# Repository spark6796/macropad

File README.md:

This is an awesome macropad with 8 buttons, 1 rotary encoder, and an OLED screen. All keys have RGB LEDs, with extra indicator LEDs at the top to show status. It runs on KMK firmware and is fully customizable.

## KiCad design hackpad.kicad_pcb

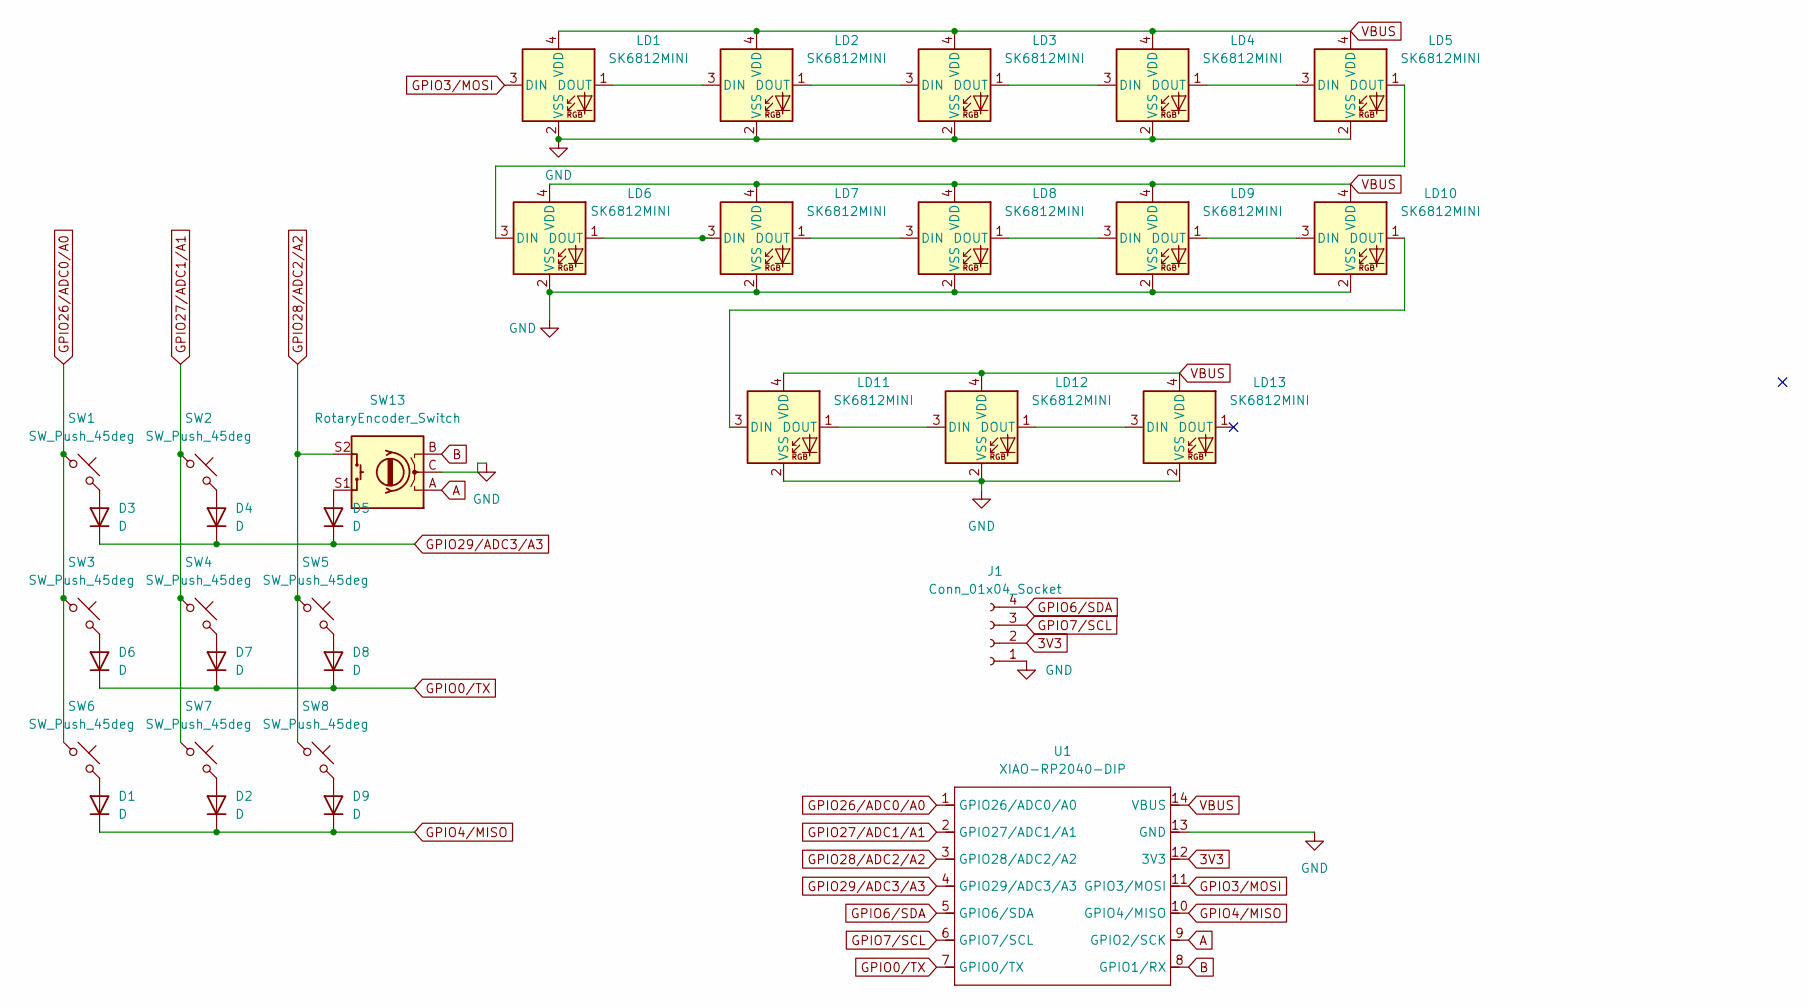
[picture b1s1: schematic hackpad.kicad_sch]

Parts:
D1, D2, D3, D4, D5, D6, D7, D8, D9: D; D_A-405_P10.16mm_Horizontal
J1: Conn_01x04_Socket; SSD1306-0.91-OLED-4pin-128x32
LD1, LD2, LD3, LD4, LD5, LD6, LD7, LD8, LD9, LD10, LD11, LD12, LD13: SK6812MINI; SK6812-MINI-E
SW1, SW2, SW3, SW4, SW5, SW6, SW7, SW8: SW_Push_45deg; SW_Cherry_MX_1.00u_PCB
SW13: RotaryEncoder_Switch; RotaryEncoder_Alps_EC11E-Switch_Vertical_H20mm
U1: XIAO-RP2040-DIP

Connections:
3V3: J1.2, U1.12 (3V3)
A: SW13.A, U1.9 (GPIO2/SCK)
B: SW13.B, U1.8 (GPIO1/RX)
GND: J1.1, LD1.2 (VSS), LD2.2 (VSS), LD3.2 (VSS), LD4.2 (VSS), LD5.2 (VSS), LD6.2 (VSS), LD7.2 (VSS), LD8.2 (VSS), LD9.2 (VSS), LD10.2 (VSS), LD11.2 (VSS), LD12.2 (VSS), LD13.2 (VSS), SW13.C, U1.13 (GND)
GPIO0/TX: D6.1 (K), D7.1 (K), D8.1 (K), U1.7 (GPIO0/TX)
GPIO3/MOSI: LD1.3 (DIN), U1.11 (GPIO3/MOSI)
GPIO4/MISO: D1.1 (K), D2.1 (K), D9.1 (K), U1.10 (GPIO4/MISO)
GPIO6/SDA: J1.4, U1.5 (GPIO6/SDA)
GPIO7/SCL: J1.3, U1.6 (GPIO7/SCL)
GPIO26/ADC0/A0: SW1.1, SW3.1, SW6.1, U1.1 (GPIO26/ADC0/A0)
GPIO27/ADC1/A1: SW2.1, SW4.1, SW7.1, U1.2 (GPIO27/ADC1/A1)
GPIO28/ADC2/A2: SW5.1, SW8.1, SW13.S2, U1.3 (GPIO28/ADC2/A2)
GPIO29/ADC3/A3: D3.1 (K), D4.1 (K), D5.1 (K), U1.4 (GPIO29/ADC3/A3)
unnamed: D1.2 (A), SW6.2
unnamed: D2.2 (A), SW7.2
unnamed: D3.2 (A), SW1.2
unnamed: D4.2 (A), SW2.2
unnamed: D5.2 (A), SW13.S1
unnamed: D6.2 (A), SW3.2
unnamed: D7.2 (A), SW4.2
unnamed: D8.2 (A), SW5.2
unnamed: D9.2 (A), SW8.2
unnamed: LD1.1 (DOUT), LD2.3 (DIN)
unnamed: LD2.1 (DOUT), LD3.3 (DIN)
unnamed: LD3.1 (DOUT), LD4.3 (DIN)
unnamed: LD4.1 (DOUT), LD5.3 (DIN)
unnamed: LD5.1 (DOUT), LD6.3 (DIN)
unnamed: LD6.1 (DOUT), LD7.3 (DIN)
unnamed: LD7.1 (DOUT), LD8.3 (DIN)
unnamed: LD8.1 (DOUT), LD9.3 (DIN)
unnamed: LD9.1 (DOUT), LD10.3 (DIN)
unnamed: LD10.1 (DOUT), LD11.3 (DIN)
unnamed: LD11.1 (DOUT), LD12.3 (DIN)
unnamed: LD12.1 (DOUT), LD13.3 (DIN)
VBUS: LD1.4 (VDD), LD2.4 (VDD), LD3.4 (VDD), LD4.4 (VDD), LD5.4 (VDD), LD6.4 (VDD), LD7.4 (VDD), LD8.4 (VDD), LD9.4 (VDD), LD10.4 (VDD), LD11.4 (VDD), LD12.4 (VDD), LD13.4 (VDD), U1.14 (VBUS)

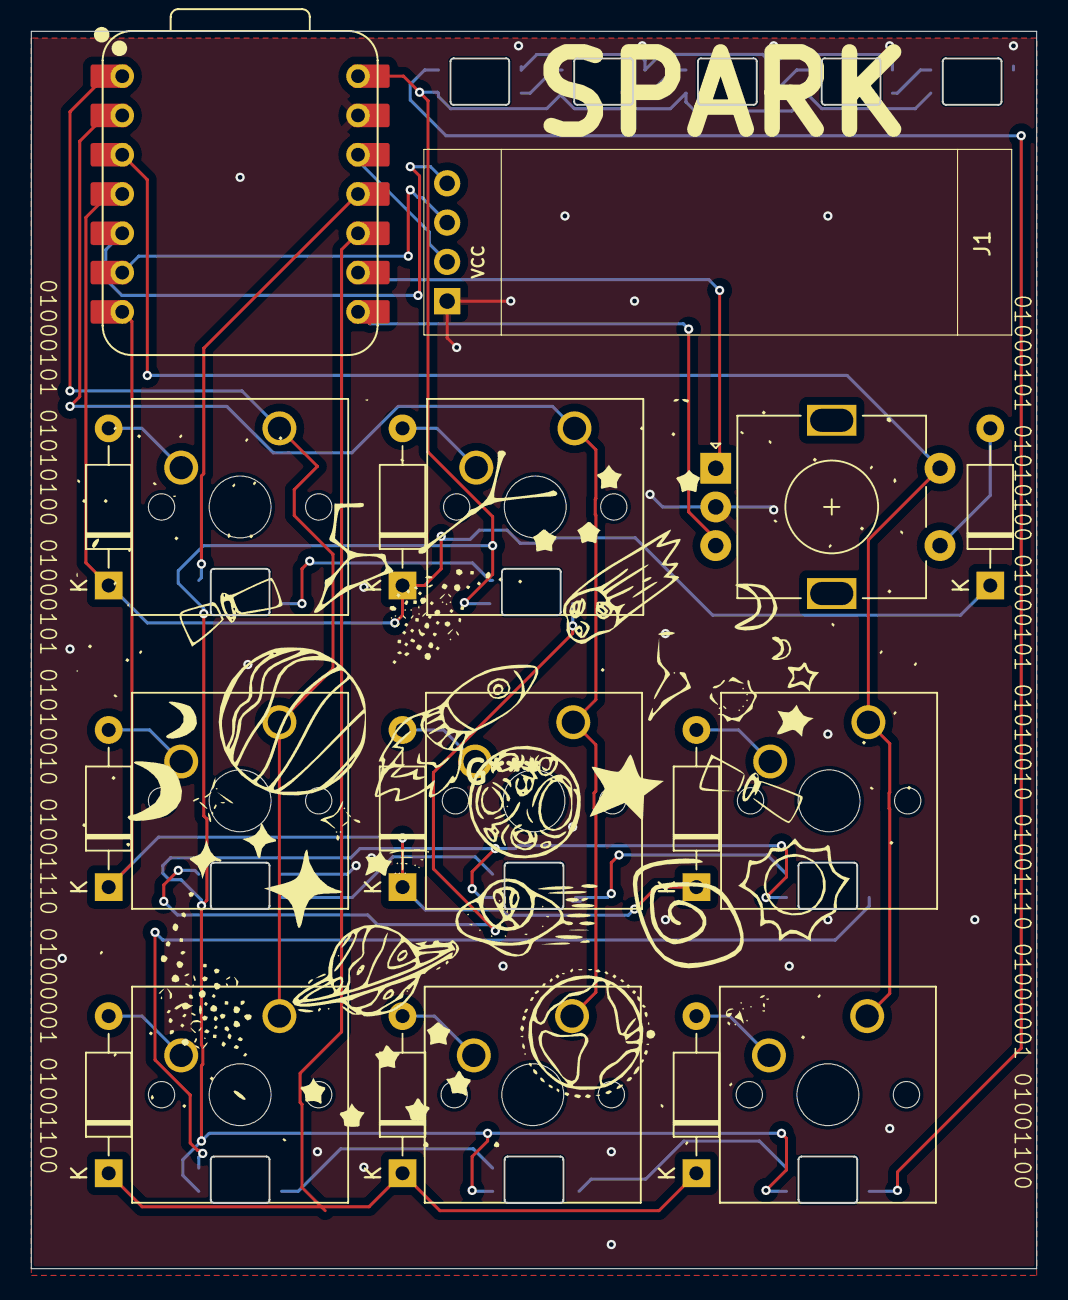
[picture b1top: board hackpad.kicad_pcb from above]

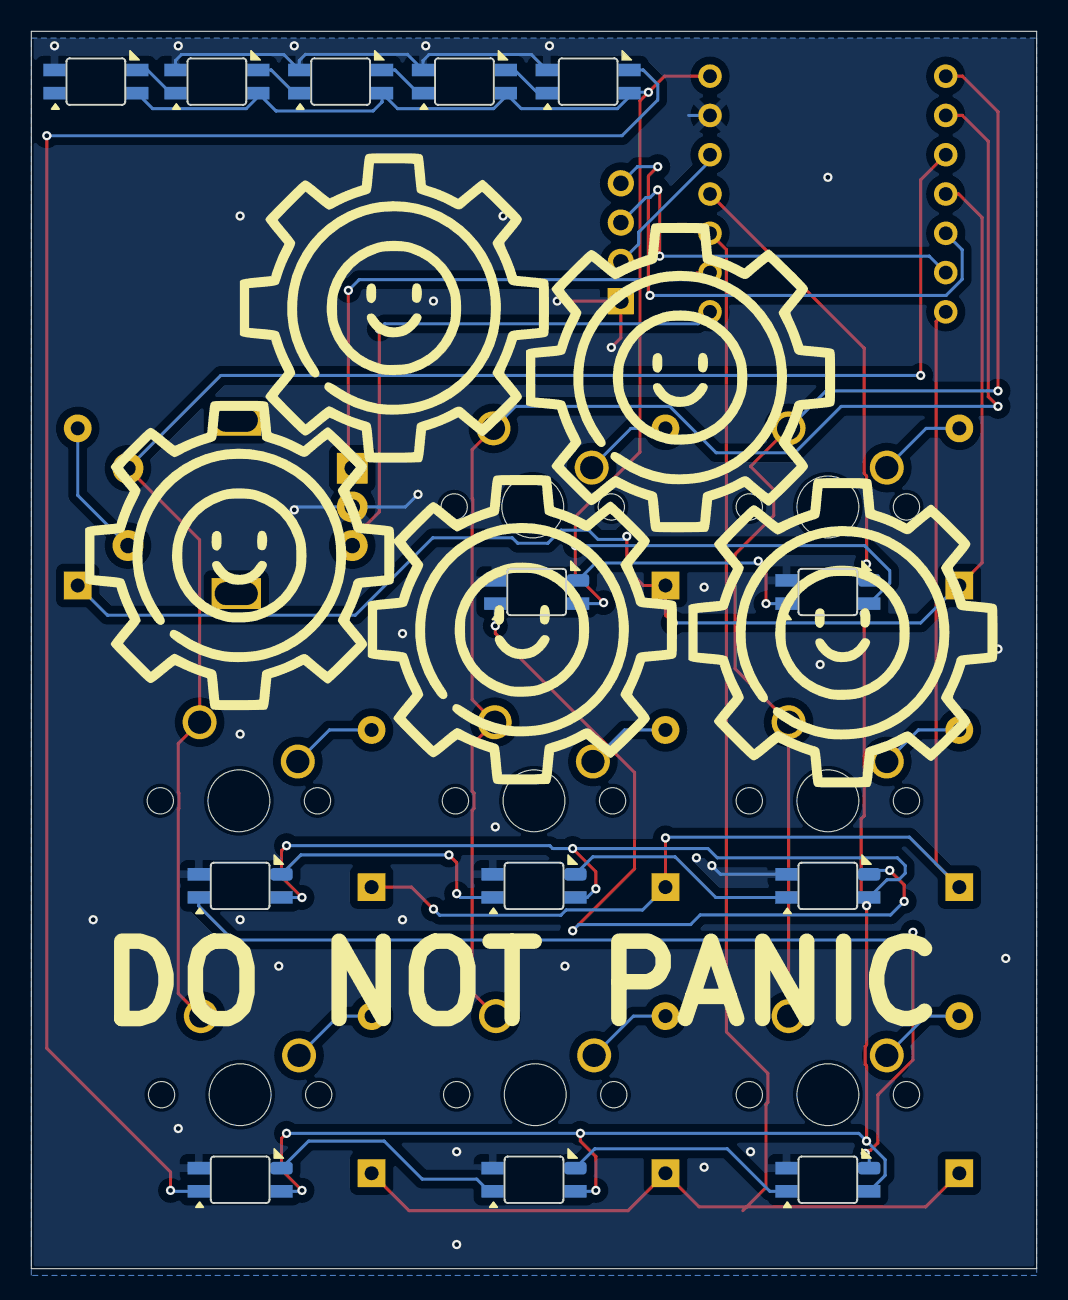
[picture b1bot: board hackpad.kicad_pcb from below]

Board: 2 copper layers, 65.0 x 80.0 mm, 33 parts (13 on the bottom side), 35 nets.

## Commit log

2025-12-18 chore: Remove duplicate files
2025-12-18 Add PCB images
2025-12-18 Add PCB top view image to README
2025-12-18 Add images
2025-12-18 Add features description for the macropad
    Added a description of the macropad features and customization.
2025-12-22 feat: Add STEP 3D models to PCB footprints
2025-12-22 Update 3D model files and PCB images
2025-12-22 feat: Add combined STEP model
2025-12-29 Add GND fill , removed via from pads
